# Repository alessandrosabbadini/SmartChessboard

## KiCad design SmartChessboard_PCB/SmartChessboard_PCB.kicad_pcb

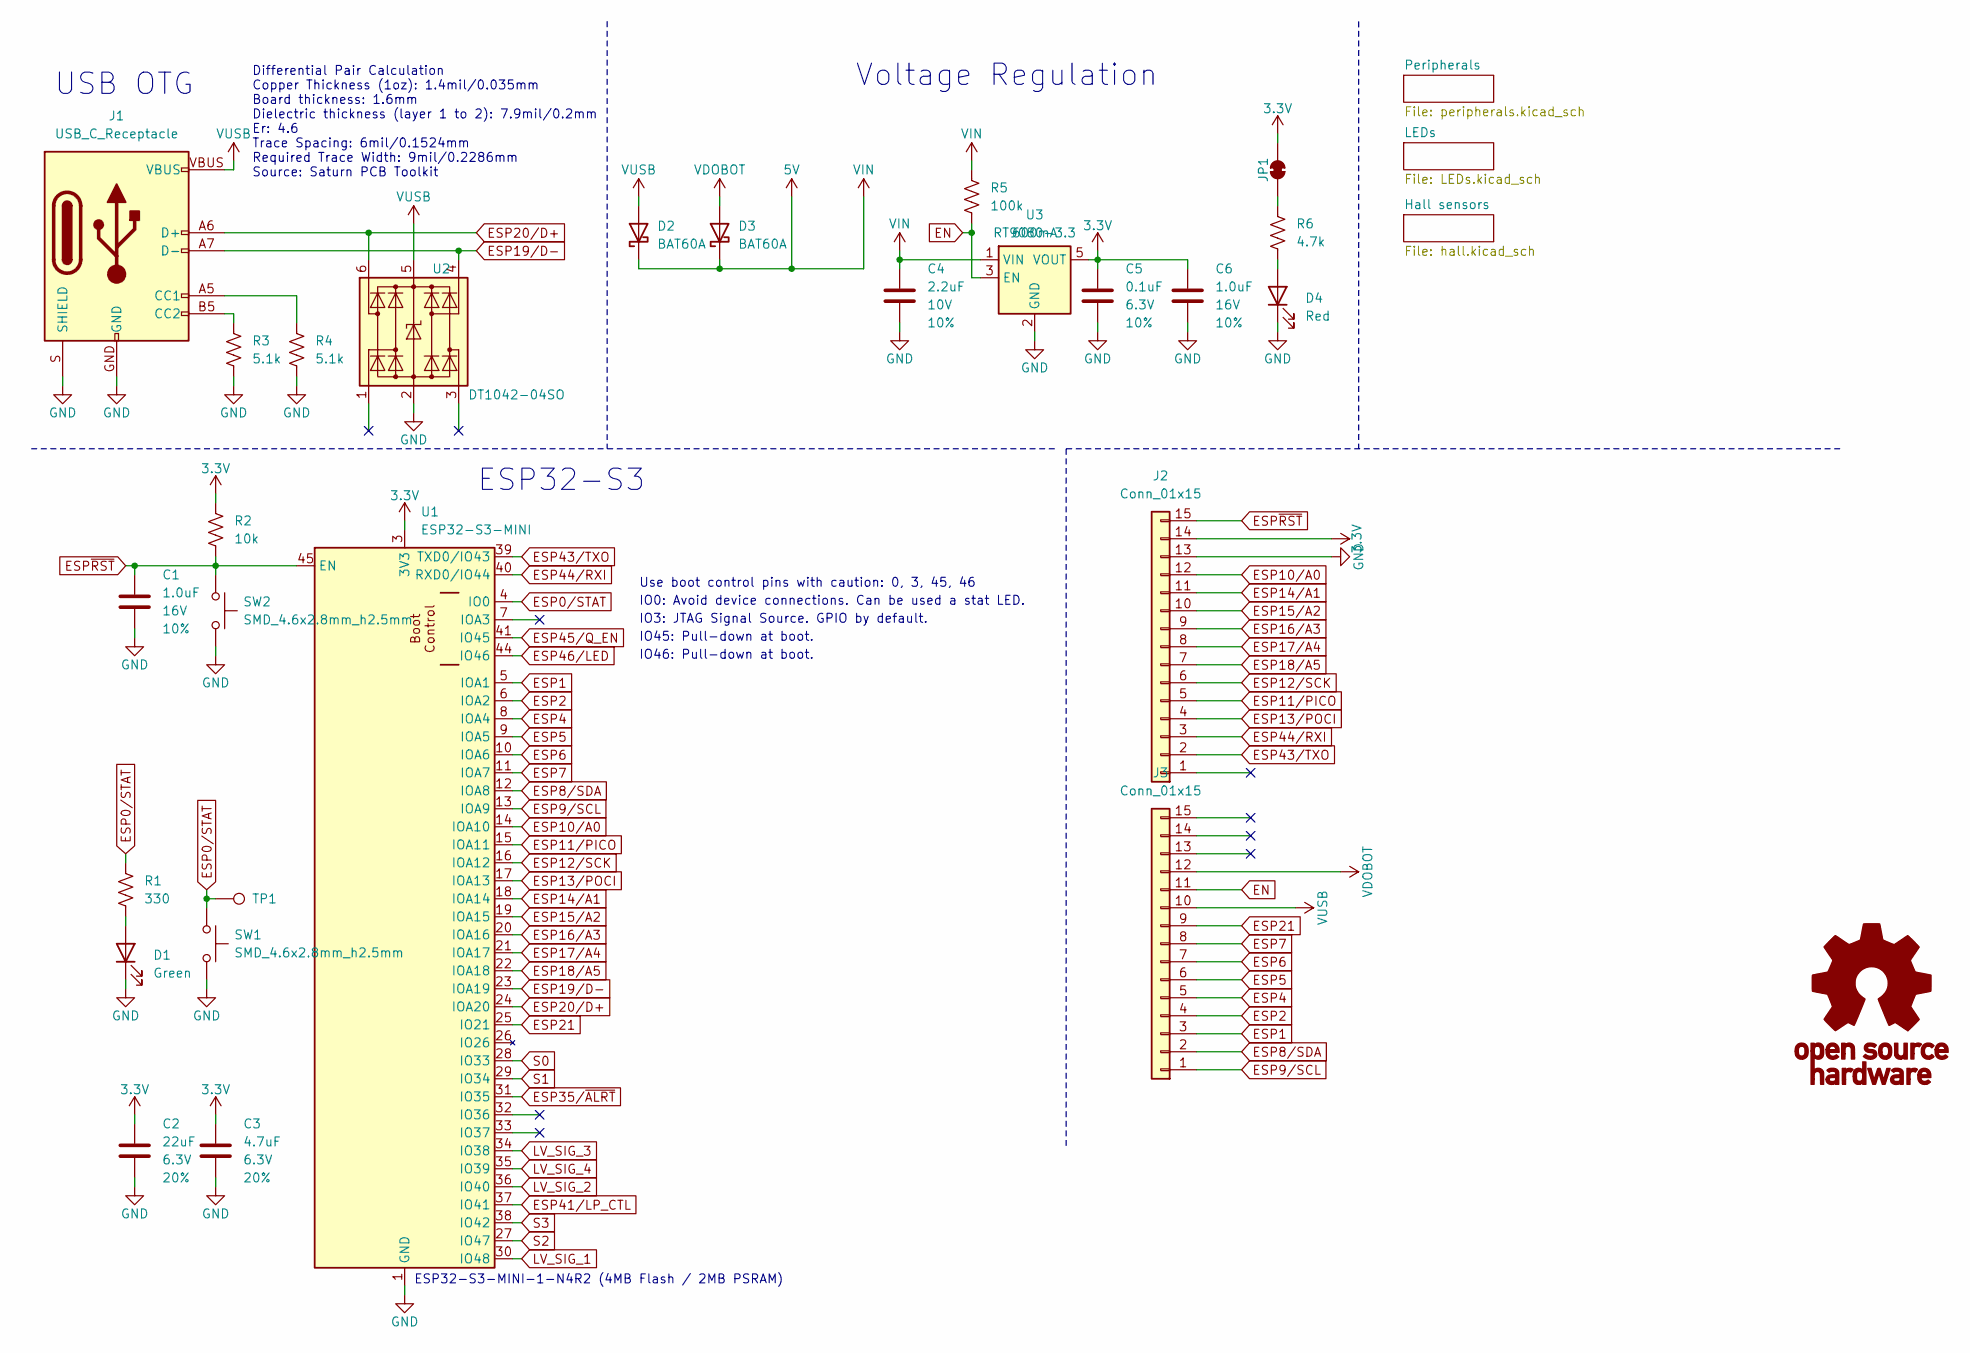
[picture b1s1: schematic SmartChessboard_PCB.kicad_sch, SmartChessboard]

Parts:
C1, C6: 1.0uF; C_0402_1005Metric; Voltage 16V; Tolerance 10%
C2: 22uF; C_0603_1608Metric; Voltage 6.3V; Tolerance 20%
C3: 4.7uF; C_0402_1005Metric; Voltage 6.3V; Tolerance 20%
C4: 2.2uF; C_0402_1005Metric; Voltage 10V; Tolerance 10%
C5: 0.1uF; C_0402_1005Metric; Voltage 6.3V; Tolerance 10%
D1: Green; LED_0603_1608Metric_Green
D2, D3: BAT60A; D_SOD-323
D4: Red; LED_0603_1608Metric_Red
G1: OSHW_Logo; Creative_Commons_License
J1: USB_C_Receptacle; USB-C_16
J2, J3: Conn_01x15; 1x15
JP1: Jumper_2_NC_Trace
R1: 330; R_0402_1005Metric
R2: 10k; R_0402_1005Metric
R3, R4: 5.1k; R_0402_1005Metric
R5: 100k; R_0402_1005Metric
R6: 4.7k; R_0402_1005Metric
SW1, SW2: SMD_4.6x2.8mm_h2.5mm; Push_SMD_4.6x2.8mm_h2.5mm
TP1: 1.0mm; TestPoint-1.0mm
U1: ESP32-S3-MINI; ESP32-MINI
U2: DT1042-04SO; SOT23-6
U3: RT9080-3.3; SOT23-5

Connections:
3.3V: C2.2, C3.1, C5.1, C6.1, J2.14, JP1.2 (B), R2.1, U1.3 (3V3), U3.5 (VOUT); also elsewhere on the board
+5V: C4.1, D2.1 (K), D3.1 (K), R5.1, U3.1 (VIN); also elsewhere on the board
EN: J3.11, R5.2, U3.3 (EN)
ESP0/STAT: R1.1, SW1.1, TP1.1, U1.4 (IO0)
ESP1: J3.3, U1.5 (IOA1)
ESP2: J3.4, U1.6 (IOA2)
ESP4: J3.5, U1.8 (IOA4)
ESP5: J3.6, U1.9 (IOA5)
ESP6: J3.7, U1.10 (IOA6)
ESP7: J3.8, U1.11 (IOA7)
ESP8/SDA: J3.2, U1.12 (IOA8); also elsewhere on the board
ESP9/SCL: J3.1, U1.13 (IOA9); also elsewhere on the board
ESP10/A0: J2.12, U1.14 (IOA10)
ESP11/PICO: J2.5, U1.15 (IOA11)
ESP12/SCK: J2.6, U1.16 (IOA12)
ESP13/POCI: J2.4, U1.17 (IOA13)
ESP14/A1: J2.11, U1.18 (IOA14)
ESP15/A2: J2.10, U1.19 (IOA15)
ESP16/A3: J2.9, U1.20 (IOA16)
ESP17/A4: J2.8, U1.21 (IOA17)
ESP18/A5: J2.7, U1.22 (IOA18)
ESP19/D-: J1.A7 (D-), J1.B7 (D-), U1.23 (IOA19), U2.4 (I/O3)
ESP20/D+: J1.A6 (D+), J1.B6 (D+), U1.24 (IOA20), U2.6 (I/O4)
ESP21: J3.9, U1.25 (IO21)
ESP35/~ALRT: U1.31 (IO35)
ESP41/LP_CTL: U1.37 (IO41)
ESP43/TXO: J2.2, U1.39 (TXD0/IO43); also elsewhere on the board
ESP44/RXI: J2.3, U1.40 (RXD0/IO44); also elsewhere on the board
ESP45/Q_EN: U1.41 (IO45); also elsewhere on the board
ESP46/LED: U1.44 (IO46); also elsewhere on the board
ESP~RST: C1.1, J2.15, R2.2, SW2.1, U1.45 (EN)
GND: C1.2, C2.1, C3.2, C4.2, C5.2, C6.2, D1.1 (K), D4.1 (K), J1.GND, J1.S (SHIELD), J2.13, R3.1, R4.2, SW1.2, SW2.2, U1.1 (GND), U1.2 (GND), U1.42 (GND), U1.43 (GND), U1.46 (GND), U1.47 (GND), U1.48 (GND), U1.49 (GND), U1.50 (GND), U1.51 (GND), U1.52 (GND), U1.53 (GND), U1.54 (GND), U1.55 (GND), U1.56 (GND), U1.57 (GND), U1.58 (GND), U1.59 (GND), U1.60 (GND), U1.61 (GND), U1.62 (GND), U1.63 (GND), U1.64 (GND), U1.65 (GND), U2.2 (GND), U3.2 (GND); also elsewhere on the board
LV_SIG_1: U1.30 (IO48); also elsewhere on the board
LV_SIG_2: U1.36 (IO40); also elsewhere on the board
LV_SIG_3: U1.34 (IO38); also elsewhere on the board
LV_SIG_4: U1.35 (IO39); also elsewhere on the board
unnamed: D1.2 (A), R1.2
unnamed: D4.2 (A), R6.2
unnamed: J1.A5 (CC1), R4.1
unnamed: J1.B5 (CC2), R3.2
unnamed: JP1.1 (A), R6.1
S0: U1.28 (IO33); also elsewhere on the board
S1: U1.29 (IO34); also elsewhere on the board
S2: U1.27 (IO47); also elsewhere on the board
S3: U1.38 (IO42); also elsewhere on the board
VDOBOT: D3.2 (A), J3.12; also elsewhere on the board
VUSB: D2.2 (A), J1.VBUS, J3.10, U2.5 (VCC)

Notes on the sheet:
IO0: Avoid device connections. Can be used a stat LED.
IO3: JTAG Signal Source. GPIO by default.
Differential Pair Calculation Copper Thickness (1oz): 1.4mil/0.035mm Board thickness: 1.6mm Dielectric thickness (layer 1 to 2): 7.9mil/0.2mm Er: 4.6 Trace Spacing: 6mil/0.1524mm Required Trace Width: 9mil/0.2286mm Source: Saturn PCB Toolkit
ESP32-S3-MINI-1-N4R2 (4MB Flash / 2MB PSRAM)
Voltage Regulation
IO45: Pull-down at boot.
Use boot control pins with caution: 0, 3, 45, 46
ESP32-S3
IO46: Pull-down at boot.
USB OTG

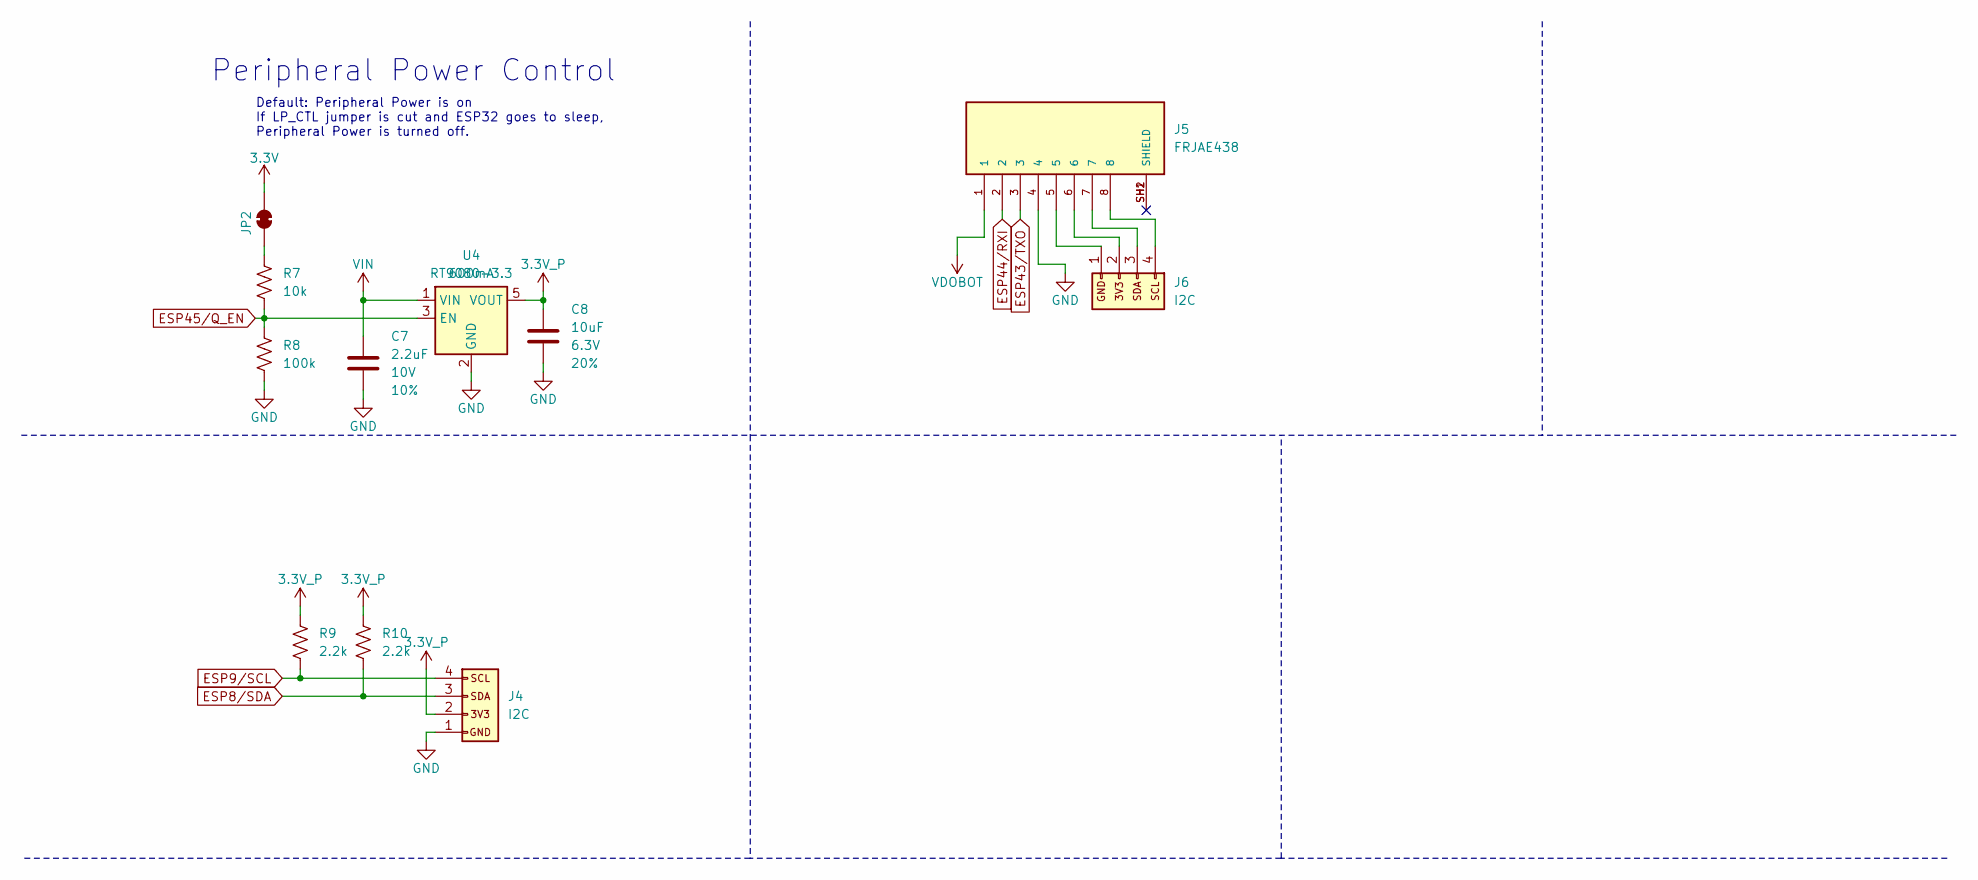
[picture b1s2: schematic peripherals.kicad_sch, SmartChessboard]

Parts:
C7: 2.2uF; C_0402_1005Metric; Voltage 10V; Tolerance 10%
C8: 10uF; C_0402_1005Metric; Voltage 6.3V; Tolerance 20%
J4, J6: I2C; 1x04
J5: FRJAE438; AMPHENOL_FRJAE438; PARTREV B
JP2: Jumper_2_NC_Trace
R7: 10k; R_0402_1005Metric
R8: 100k; R_0402_1005Metric
R9, R10: 2.2k; R_0402_1005Metric
U4: RT9080-3.3; SOT23-5

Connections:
3.3V: JP2.2 (B); also elsewhere on the board
3.3V_P: C8.1, J4.2, R9.1, R10.1, U4.5 (VOUT)
5V: C7.1, U4.1 (VIN)
ESP8/SDA: J4.3, R10.2; also elsewhere on the board
ESP9/SCL: J4.4, R9.2; also elsewhere on the board
ESP43/TXO: J5.3; also elsewhere on the board
ESP44/RXI: J5.2; also elsewhere on the board
ESP45/Q_EN: R7.2, R8.1, U4.3 (EN); also elsewhere on the board
GND: C7.2, C8.2, J4.1, J5.4, R8.2, U4.2 (GND); also elsewhere on the board
unnamed: J5.5, J6.1
unnamed: J5.6, J6.2
unnamed: J5.7, J6.3
unnamed: J5.8, J6.4
unnamed: JP2.1 (A), R7.1
VDOBOT: J5.1; also elsewhere on the board

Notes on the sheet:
Peripheral Power Control
Default: Peripheral Power is on If LP_CTL jumper is cut and ESP32 goes to sleep, Peripheral Power is turned off.

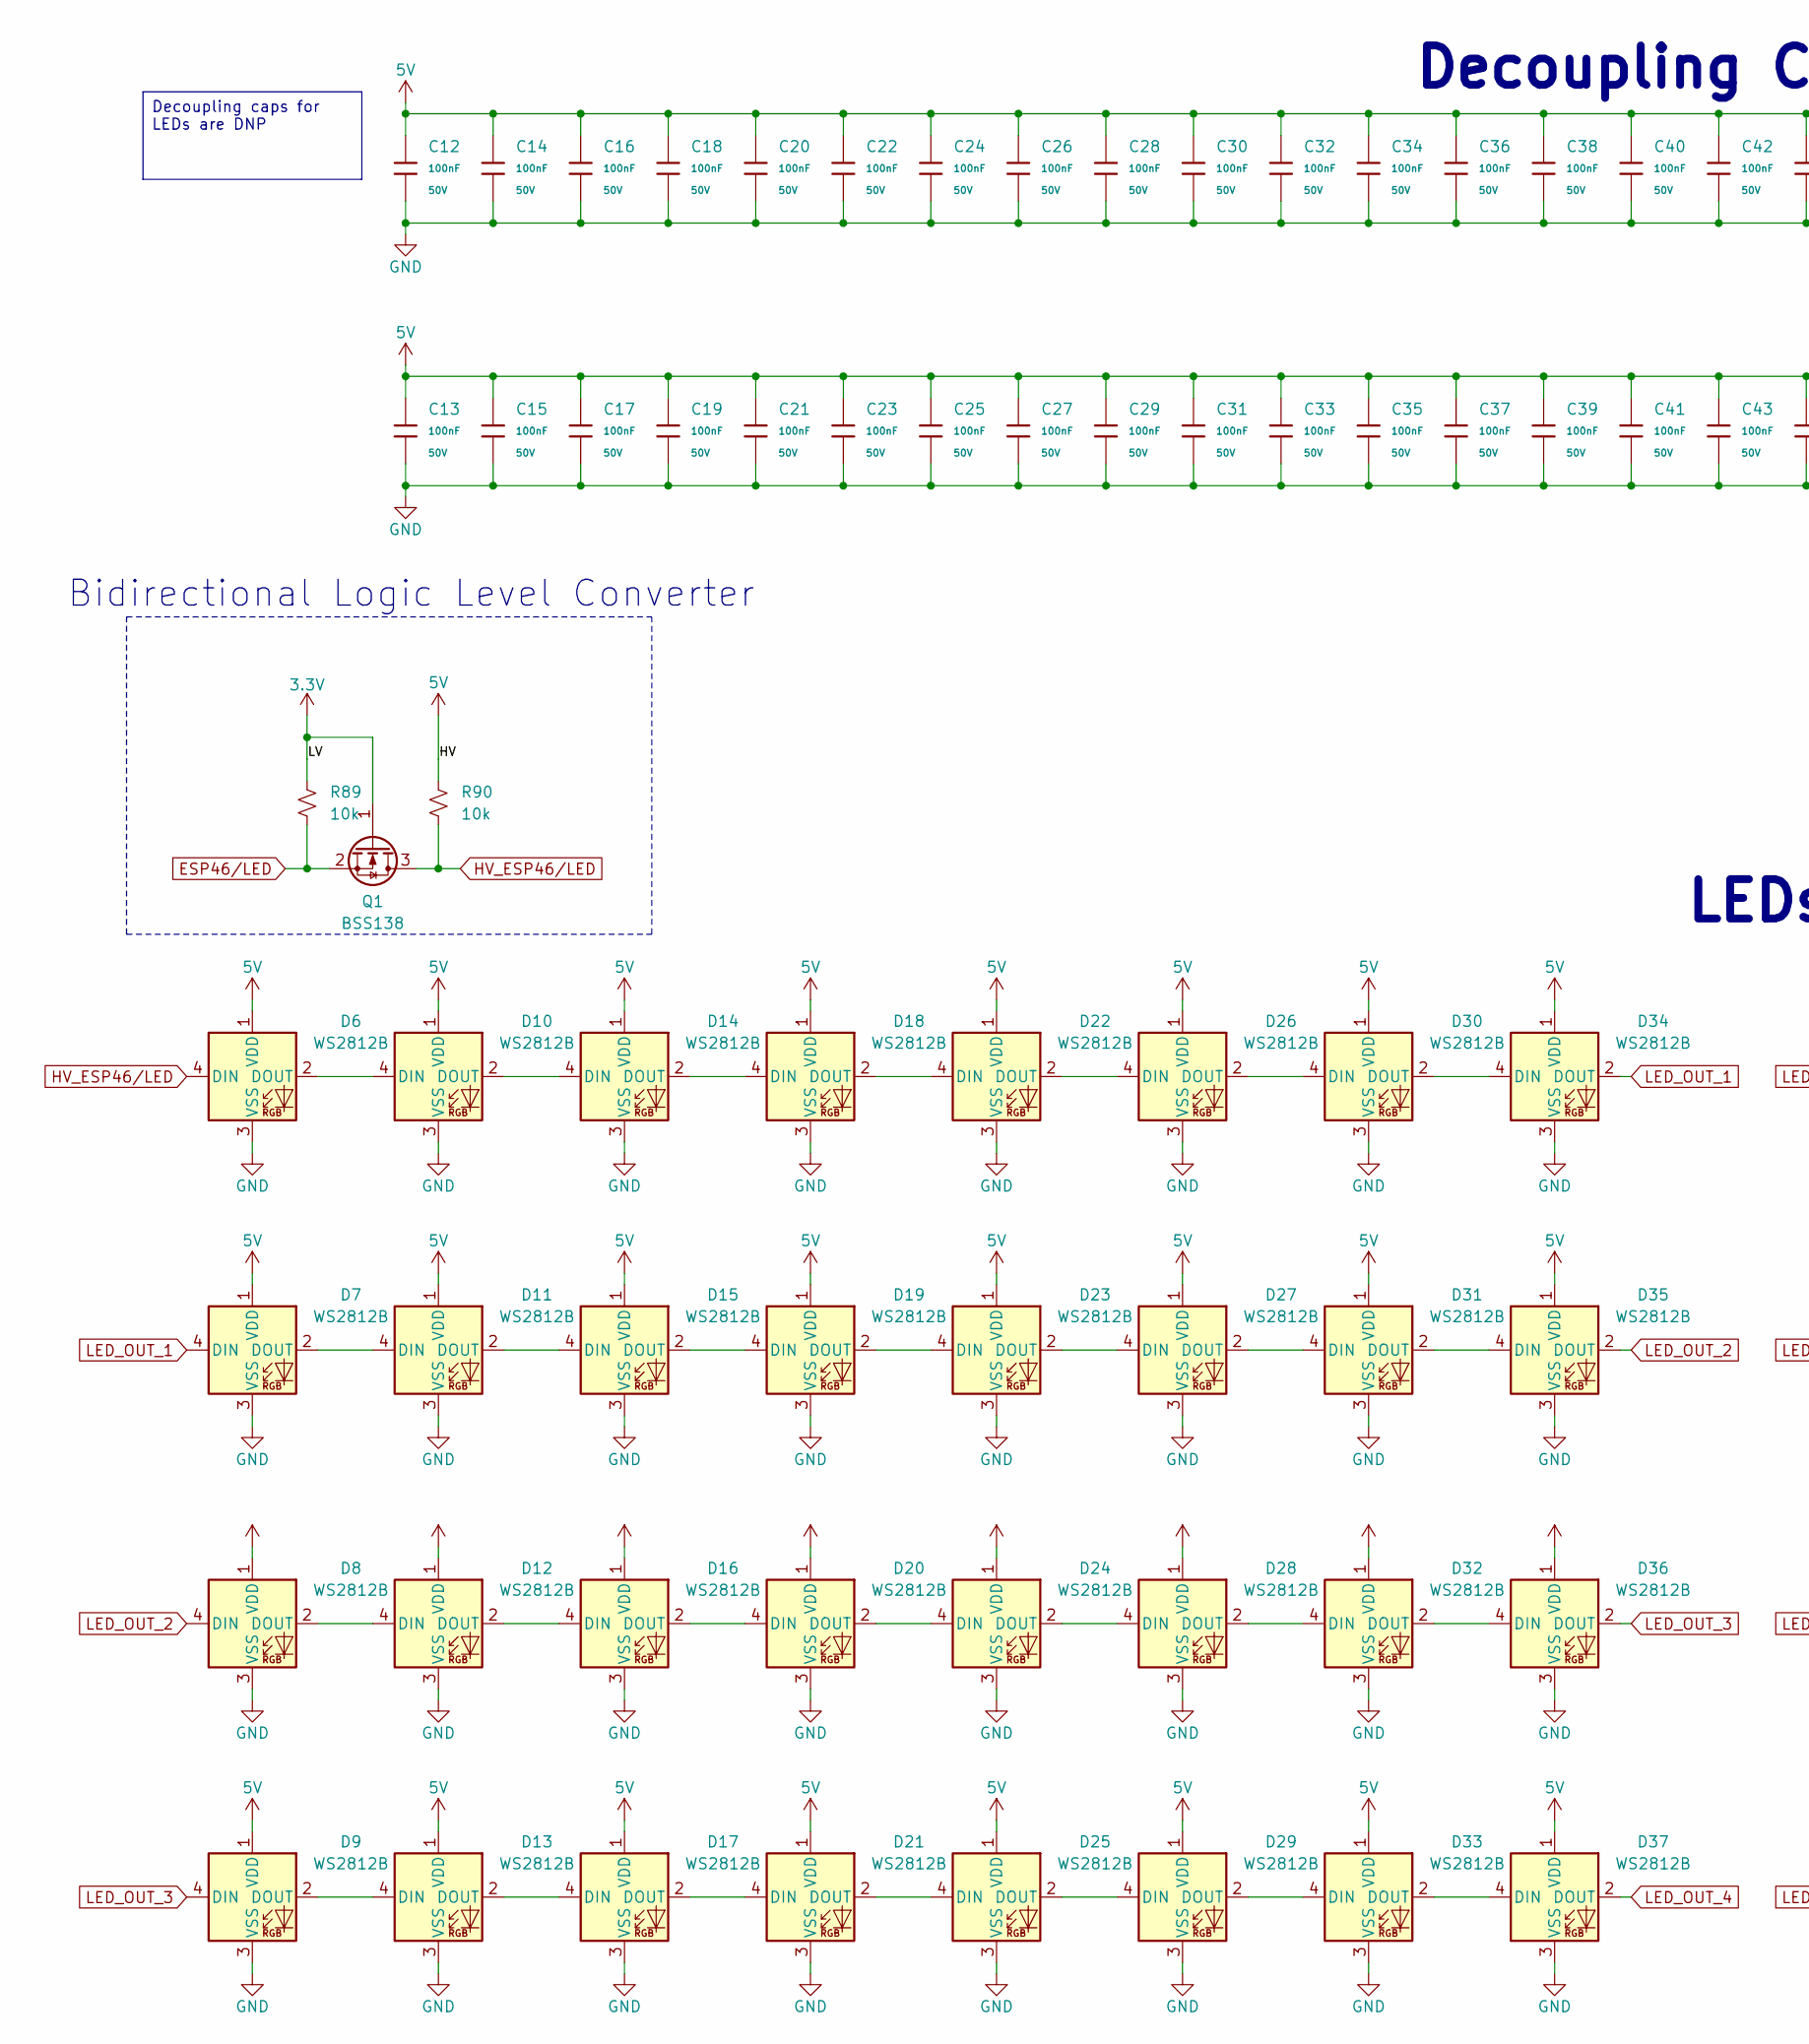
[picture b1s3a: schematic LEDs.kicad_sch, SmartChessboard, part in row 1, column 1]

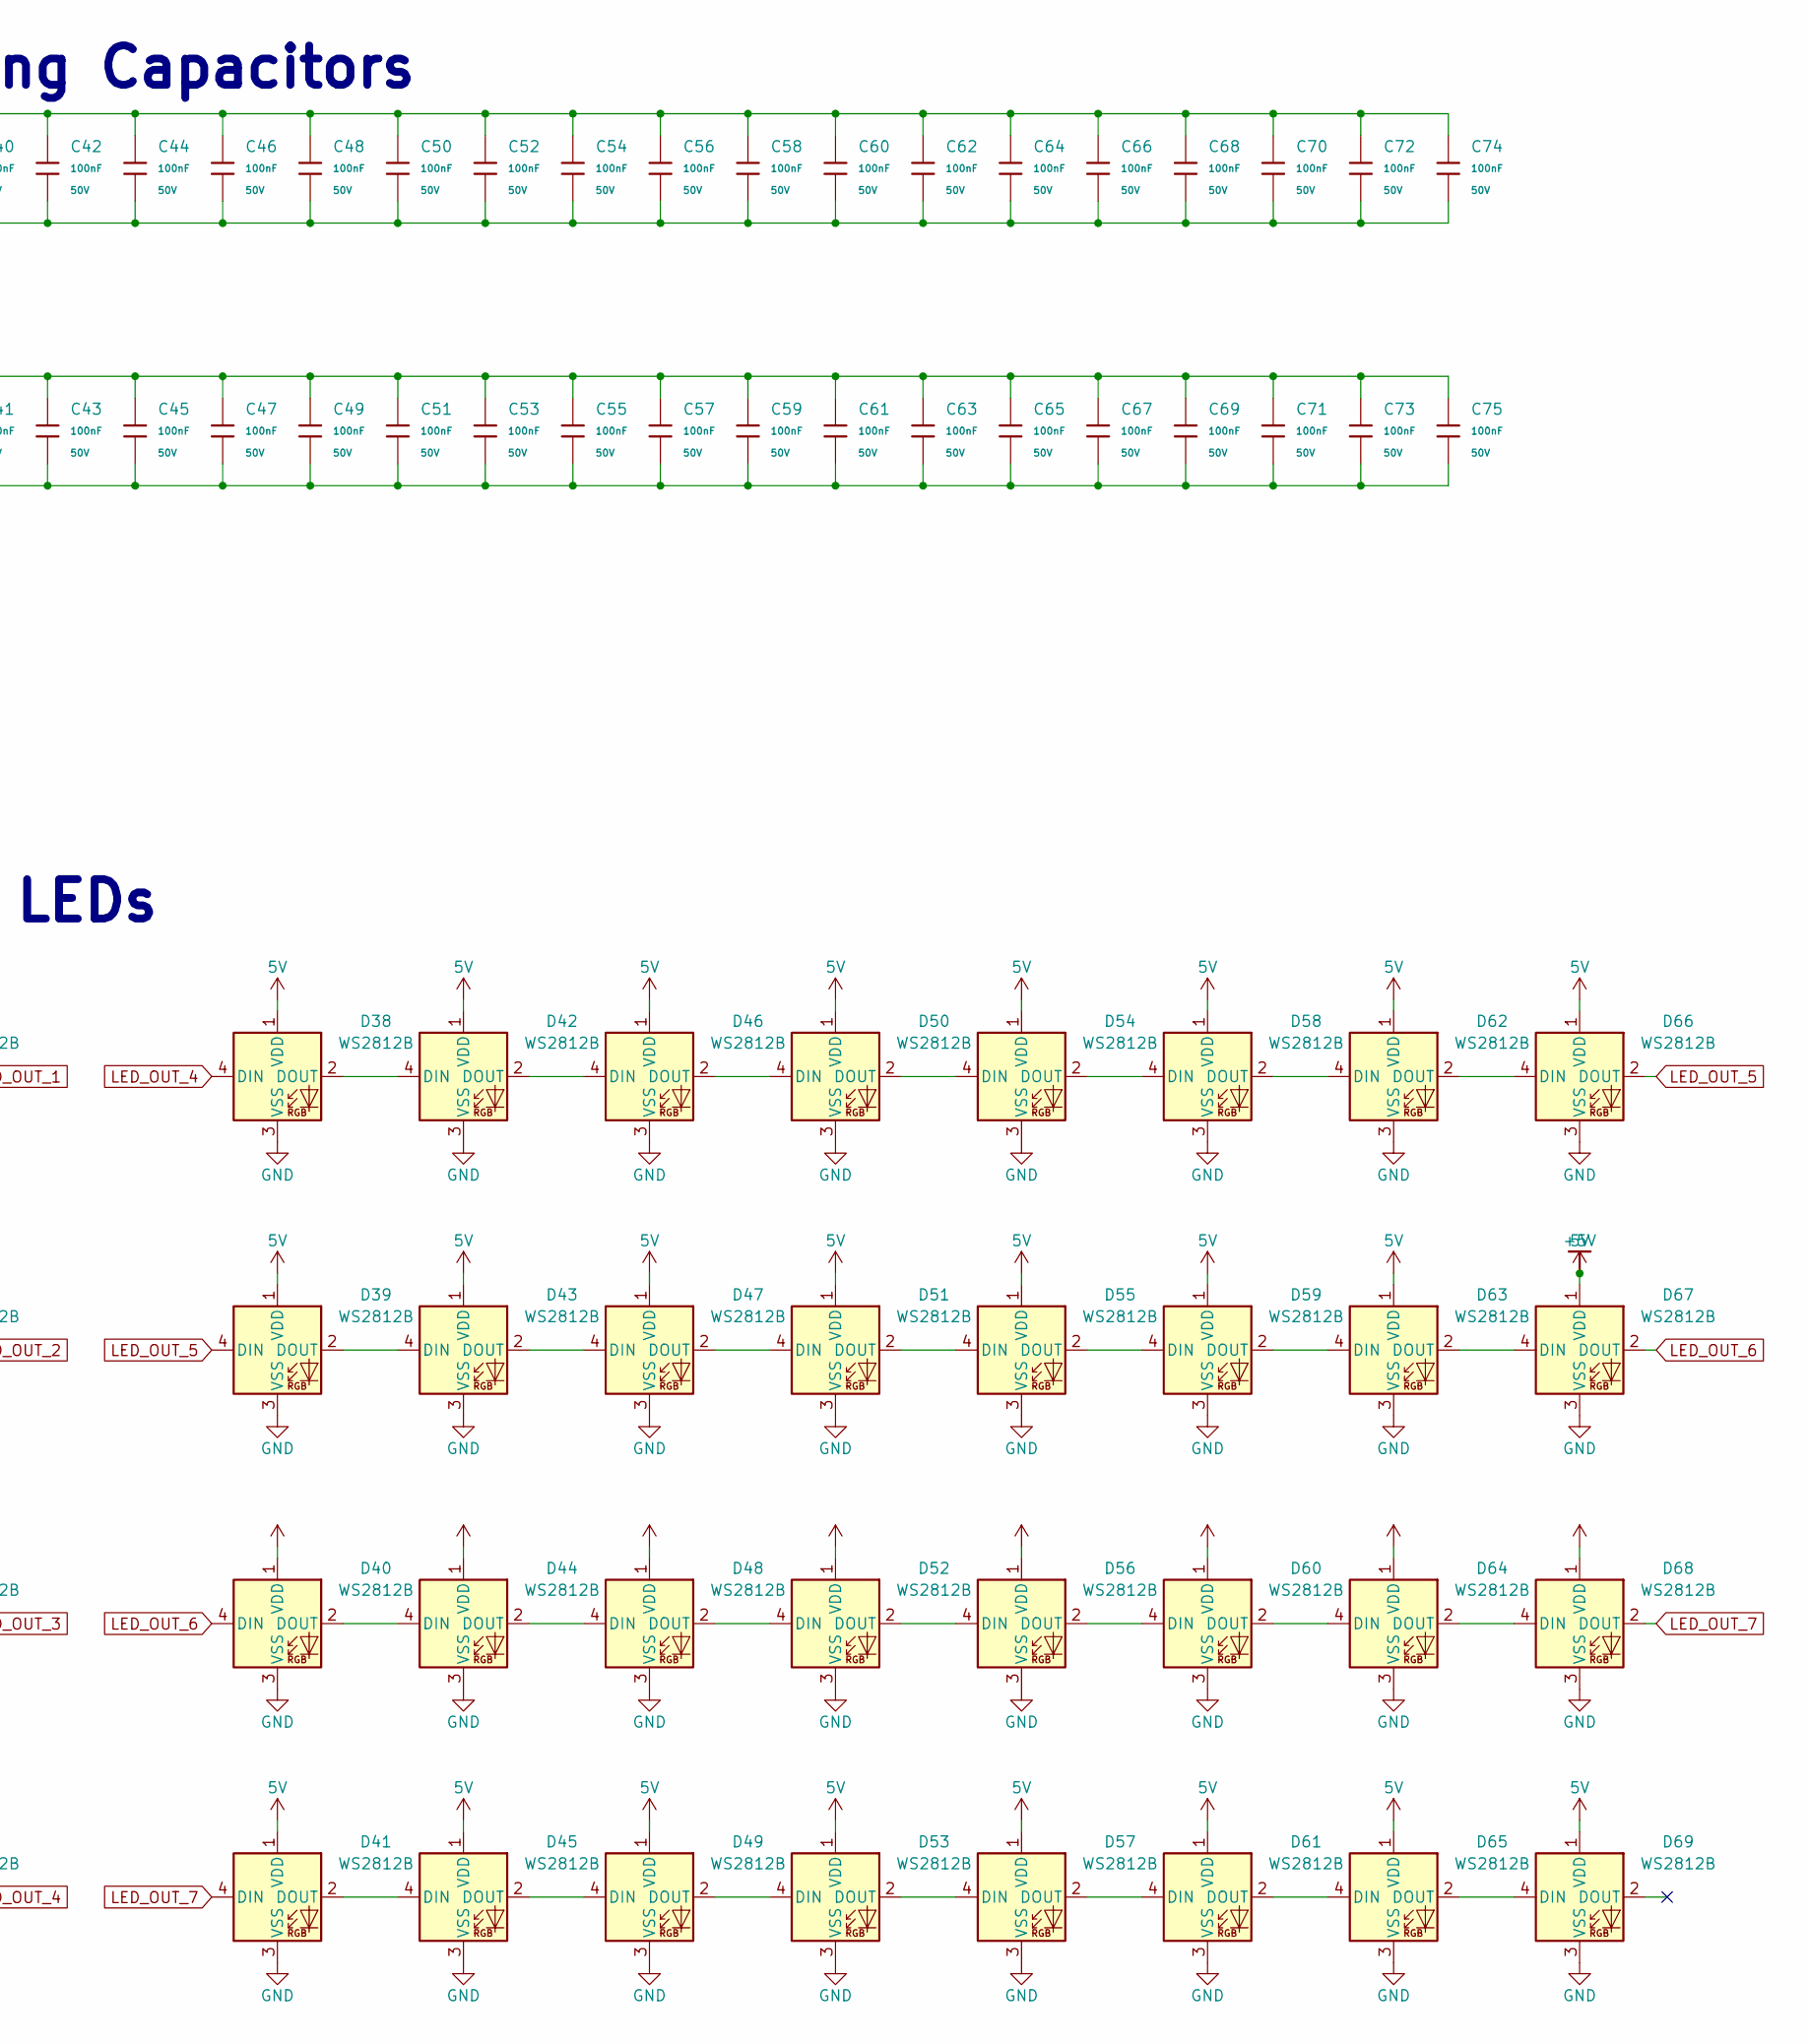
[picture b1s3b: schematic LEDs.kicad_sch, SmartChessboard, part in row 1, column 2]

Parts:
C12, C13, C14, C15, C16, C17, C18, C19, C20, C21, C22, C23, C24, C25, C26, C27, C28, C29, C30, C31, C32, C33, C34, C35, C36, C37, C38, C39, C40, C41, C42, C43, C44, C45, C46, C47, C48, C49, C50, C51, C52, C53, C54, C55, C56, C57, C58, C59, C60, C61, C62, C63, C64, C65, C66, C67, C68, C69, C70, C71, C72, C73, C74, C75: 100nF; C_0402; Voltage Rated 50V; Tolerance ±10%; Part CL05B104KB54PNC; LCSC C307331
D6, D7, D8, D9, D10, D11, D12, D13, D14, D15, D16, D17, D18, D19, D20, D21, D22, D23, D24, D25, D26, D27, D28, D29, D30, D31, D32, D33, D34, D35, D36, D37, D38, D39, D40, D41, D42, D43, D44, D45, D46, D47, D48, D49, D50, D51, D52, D53, D54, D55, D56, D57, D58, D59, D60, D61, D62, D63, D64, D65, D66, D67, D68, D69: WS2812B; LED_WS2812B_PLCC4_5.0x5.0mm_P3.2mm
Q1: BSS138; SOT-23
R89, R90: 10k; R_0402_1005Metric

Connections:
3.3V: Q1.1 (G), R89.1; also elsewhere on the board
+5V: C12.1, C13.1, C14.1, C15.1, C16.1, C17.1, C18.1, C19.1, C20.1, C21.1, C22.1, C23.1, C24.1, C25.1, C26.1, C27.1, C28.1, C29.1, C30.1, C31.1, C32.1, C33.1, C34.1, C35.1, C36.1, C37.1, C38.1, C39.1, C40.1, C41.1, C42.1, C43.1, C44.1, C45.1, C46.1, C47.1, C48.1, C49.1, C50.1, C51.1, C52.1, C53.1, C54.1, C55.1, C56.1, C57.1, C58.1, C59.1, C60.1, C61.1, C62.1, C63.1, C64.1, C65.1, C66.1, C67.1, C68.1, C69.1, C70.1, C71.1, C72.1, C73.1, C74.1, C75.1, D6.1 (VDD), D7.1 (VDD), D8.1 (VDD), D9.1 (VDD), D10.1 (VDD), D11.1 (VDD), D12.1 (VDD), D13.1 (VDD), D14.1 (VDD), D15.1 (VDD), D16.1 (VDD), D17.1 (VDD), D18.1 (VDD), D19.1 (VDD), D20.1 (VDD), D21.1 (VDD), D22.1 (VDD), D23.1 (VDD), D24.1 (VDD), D25.1 (VDD), D26.1 (VDD), D27.1 (VDD), D28.1 (VDD), D29.1 (VDD), D30.1 (VDD), D31.1 (VDD), D32.1 (VDD), D33.1 (VDD), D34.1 (VDD), D35.1 (VDD), D36.1 (VDD), D37.1 (VDD), D38.1 (VDD), D39.1 (VDD), D40.1 (VDD), D41.1 (VDD), D42.1 (VDD), D43.1 (VDD), D44.1 (VDD), D45.1 (VDD), D46.1 (VDD), D47.1 (VDD), D48.1 (VDD), D49.1 (VDD), D50.1 (VDD), D51.1 (VDD), D52.1 (VDD), D53.1 (VDD), D54.1 (VDD), D55.1 (VDD), D56.1 (VDD), D57.1 (VDD), D58.1 (VDD), D59.1 (VDD), D60.1 (VDD), D61.1 (VDD), D62.1 (VDD), D63.1 (VDD), D64.1 (VDD), D65.1 (VDD), D66.1 (VDD), D67.1 (VDD), D68.1 (VDD), D69.1 (VDD), R90.1; also elsewhere on the board
ESP46/LED: Q1.2 (S), R89.2; also elsewhere on the board
GND: C12.2, C13.2, C14.2, C15.2, C16.2, C17.2, C18.2, C19.2, C20.2, C21.2, C22.2, C23.2, C24.2, C25.2, C26.2, C27.2, C28.2, C29.2, C30.2, C31.2, C32.2, C33.2, C34.2, C35.2, C36.2, C37.2, C38.2, C39.2, C40.2, C41.2, C42.2, C43.2, C44.2, C45.2, C46.2, C47.2, C48.2, C49.2, C50.2, C51.2, C52.2, C53.2, C54.2, C55.2, C56.2, C57.2, C58.2, C59.2, C60.2, C61.2, C62.2, C63.2, C64.2, C65.2, C66.2, C67.2, C68.2, C69.2, C70.2, C71.2, C72.2, C73.2, C74.2, C75.2, D6.3 (VSS), D7.3 (VSS), D8.3 (VSS), D9.3 (VSS), D10.3 (VSS), D11.3 (VSS), D12.3 (VSS), D13.3 (VSS), D14.3 (VSS), D15.3 (VSS), D16.3 (VSS), D17.3 (VSS), D18.3 (VSS), D19.3 (VSS), D20.3 (VSS), D21.3 (VSS), D22.3 (VSS), D23.3 (VSS), D24.3 (VSS), D25.3 (VSS), D26.3 (VSS), D27.3 (VSS), D28.3 (VSS), D29.3 (VSS), D30.3 (VSS), D31.3 (VSS), D32.3 (VSS), D33.3 (VSS), D34.3 (VSS), D35.3 (VSS), D36.3 (VSS), D37.3 (VSS), D38.3 (VSS), D39.3 (VSS), D40.3 (VSS), D41.3 (VSS), D42.3 (VSS), D43.3 (VSS), D44.3 (VSS), D45.3 (VSS), D46.3 (VSS), D47.3 (VSS), D48.3 (VSS), D49.3 (VSS), D50.3 (VSS), D51.3 (VSS), D52.3 (VSS), D53.3 (VSS), D54.3 (VSS), D55.3 (VSS), D56.3 (VSS), D57.3 (VSS), D58.3 (VSS), D59.3 (VSS), D60.3 (VSS), D61.3 (VSS), D62.3 (VSS), D63.3 (VSS), D64.3 (VSS), D65.3 (VSS), D66.3 (VSS), D67.3 (VSS), D68.3 (VSS), D69.3 (VSS); also elsewhere on the board
HV_ESP46/LED: D6.4 (DIN), Q1.3 (D), R90.2
LED_OUT_1: D7.4 (DIN), D34.2 (DOUT)
LED_OUT_2: D8.4 (DIN), D35.2 (DOUT)
LED_OUT_3: D9.4 (DIN), D36.2 (DOUT)
LED_OUT_4: D37.2 (DOUT), D38.4 (DIN)
LED_OUT_5: D39.4 (DIN), D66.2 (DOUT)
LED_OUT_6: D40.4 (DIN), D67.2 (DOUT)
LED_OUT_7: D41.4 (DIN), D68.2 (DOUT)
unnamed: D6.2 (DOUT), D10.4 (DIN)
unnamed: D10.2 (DOUT), D14.4 (DIN)
unnamed: D7.2 (DOUT), D11.4 (DIN)
unnamed: D11.2 (DOUT), D15.4 (DIN)
unnamed: D8.2 (DOUT), D12.4 (DIN)
unnamed: D12.2 (DOUT), D16.4 (DIN)
unnamed: D9.2 (DOUT), D13.4 (DIN)
unnamed: D13.2 (DOUT), D17.4 (DIN)
unnamed: D14.2 (DOUT), D18.4 (DIN)
unnamed: D15.2 (DOUT), D19.4 (DIN)
unnamed: D16.2 (DOUT), D20.4 (DIN)
unnamed: D17.2 (DOUT), D21.4 (DIN)
unnamed: D18.2 (DOUT), D22.4 (DIN)
unnamed: D19.2 (DOUT), D23.4 (DIN)
unnamed: D20.2 (DOUT), D24.4 (DIN)
unnamed: D21.2 (DOUT), D25.4 (DIN)
unnamed: D22.2 (DOUT), D26.4 (DIN)
unnamed: D23.2 (DOUT), D27.4 (DIN)
unnamed: D24.2 (DOUT), D28.4 (DIN)
unnamed: D25.2 (DOUT), D29.4 (DIN)
unnamed: D26.2 (DOUT), D30.4 (DIN)
unnamed: D27.2 (DOUT), D31.4 (DIN)
unnamed: D28.2 (DOUT), D32.4 (DIN)
unnamed: D29.2 (DOUT), D33.4 (DIN)
unnamed: D30.2 (DOUT), D34.4 (DIN)
unnamed: D31.2 (DOUT), D35.4 (DIN)
unnamed: D32.2 (DOUT), D36.4 (DIN)
unnamed: D33.2 (DOUT), D37.4 (DIN)
unnamed: D38.2 (DOUT), D42.4 (DIN)
unnamed: D39.2 (DOUT), D43.4 (DIN)
unnamed: D40.2 (DOUT), D44.4 (DIN)
unnamed: D41.2 (DOUT), D45.4 (DIN)
unnamed: D42.2 (DOUT), D46.4 (DIN)
unnamed: D43.2 (DOUT), D47.4 (DIN)
unnamed: D44.2 (DOUT), D48.4 (DIN)
unnamed: D45.2 (DOUT), D49.4 (DIN)
unnamed: D46.2 (DOUT), D50.4 (DIN)
unnamed: D47.2 (DOUT), D51.4 (DIN)
unnamed: D48.2 (DOUT), D52.4 (DIN)
unnamed: D49.2 (DOUT), D53.4 (DIN)
unnamed: D50.2 (DOUT), D54.4 (DIN)
unnamed: D51.2 (DOUT), D55.4 (DIN)
unnamed: D52.2 (DOUT), D56.4 (DIN)
unnamed: D53.2 (DOUT), D57.4 (DIN)
unnamed: D54.2 (DOUT), D58.4 (DIN)
unnamed: D55.2 (DOUT), D59.4 (DIN)
unnamed: D56.2 (DOUT), D60.4 (DIN)
unnamed: D57.2 (DOUT), D61.4 (DIN)
unnamed: D58.2 (DOUT), D62.4 (DIN)
unnamed: D59.2 (DOUT), D63.4 (DIN)
unnamed: D60.2 (DOUT), D64.4 (DIN)
unnamed: D61.2 (DOUT), D65.4 (DIN)
unnamed: D62.2 (DOUT), D66.4 (DIN)
unnamed: D63.2 (DOUT), D67.4 (DIN)
unnamed: D64.2 (DOUT), D68.4 (DIN)
unnamed: D65.2 (DOUT), D69.4 (DIN)

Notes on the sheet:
LEDs
Bidirectional Logic Level Converter
Decoupling Capacitors
Decoupling caps for LEDs are DNP

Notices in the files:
SmartChessboard_PCB/LEDs.kicad_sch:
Released under CERN Open Hardware Licence Version 2
parts and their libraries:
Released under the Creative Commons Attribution Share-Alike 4.0 License
https://creativecommons.org/licenses/by-sa/4.0
